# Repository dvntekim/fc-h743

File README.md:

# fc-h743 — STM32H743 flight controller for a GPS-denied learned-control quadrotor

> **DRAFT UNTIL INDEPENDENT REVIEW.** Not yet reviewed by a second engineer and not ordered.
> Work through [REVIEW.md](REVIEW.md) before anyone pays for boards.

· [Changelog](CHANGELOG.md) · [Build log](docs/BUILD_LOG.md) · [Design review](docs/design_review.md) · [Contributing](CONTRIBUTING.md)

**View it in the browser (no install):**
- Whole project (board + all 7 schematic sheets): <https://kicanvas.org/?github=https://github.com/dvntekim/fc-h743/tree/main/kicad>
- PCB only: <https://kicanvas.org/?github=https://github.com/dvntekim/fc-h743/blob/main/kicad/fc.kicad_pcb>
- PDF schematic: [docs/schematic.pdf](docs/schematic.pdf)

| Top | Bottom |
|---|---|
|  |  |

## What it is

A 50 × 50 mm, 6-layer flight controller (30.5 mm M3 mount) that runs PX4 on an STM32H743VIT6.
It is adapted from the Pixhawk FMUv6C reference design (same MCU family, LQFP-100, same PX4 pin
roles where possible) and built for indoor, GPS-denied flight with a learned (RAPTOR-style)
controller, so the electrical effort goes into clean sensing, timing and telemetry:

| Area | What is on the board | Why |
|---|---|---|
| Primary IMU | TDK ICM-45686 on SPI1, **clocked by a 32 kHz reference from TIM2_CH3 (PB10)** | Locks the IMU's ODR to the MCU clock: no sample-rate drift between IMU and controller. PX4 `icm45686 -C 32000` |
| Second IMU | Bosch BMI088 on its own bus (SPI2) | Vibration-robust accel; independent bus so one faulty sensor cannot stall the other |
| IMU thermal control | 4 × 120 Ω heater ring around both IMUs, AO3400A on PB9 | Holds the IMUs at 45 °C so bias does not drift with ambient (PX4 `HEATER1_TEMP`) |
| Barometer | Bosch BMP581 on I2C4 (0x47) | Lowest-noise MEMS baro in the class |
| CAN | 2 × TI TCAN1462V, CAN FD with signal improvement (8 Mbit/s) | DroneCAN/Cyphal sensors (flow, range) at FD rates |
| Motor outputs | 4 × bidirectional DShot on TIM1 + ESC serial telemetry (UART8) | RPM feedback for motor-aware learned control |
| Camera trigger | M7/M8 on TIM5 (capture/trigger) | Hardware timestamps for visual odometry |
| Power | TPS54360B 5.09 V buck (60 V in, switch node as a 26 mm² pour, boot loop 2.3 mm), ideal-diode OR with USB (2 × LM66100), TLV62569 3V3, LP5907 sensor LDO, 2 × TPS2553 current-limited switches | Sensor rail can be power-cycled from firmware (PB2) to recover a hung sensor |
| Storage / USB | microSD on SDMMC2 (4-bit), USB-C (FS) | Logs and parameters; PX4 console |

## What is real and what is simulated

Nothing on this page has been built. The board has passed every check that can run without
hardware: rule checks, a JLCPCB manufacturing check, field-solver, voltage-drop and thermal
models, a power-stage simulation, and PX4 booting on a simulated STM32H743 with this board's pin
map. Each model states its limits in its own file. The first built board must confirm the
numbers, starting with the bench plan in [REVIEW.md](REVIEW.md).

Rev B is in progress: [docs/revB_thermal.md](docs/revB_thermal.md) sets an IMU temperature
requirement from the datasheets and shows the IMUs must move off the MCU onto an isolated island
to meet it. The analysis is done; the layout is not.

## Verification status

| Check | Tool | Result |
|---|---|---|
| Electrical rules | KiCad 9 ERC | **0 errors, 0 warnings** |
| Design rules | KiCad 9 DRC (JLCPCB 6-layer limits, `kicad/fc.kicad_dru`) | **0 errors, 0 unconnected** (61 silkscreen-cosmetic warnings) |
| Schematic ↔ PCB parity | KiCad 9 DRC `--schematic-parity` | 0 issues |
| Vendor guides | every IC against its datasheet / layout guide | [docs/design_review.md](docs/design_review.md): 4 fixes made, 4 items open |
| Pin map | `scripts/pinmap_check.py` against ST's pin data (KiCad STM32H743VITx symbol) | **PASS**, 74 pins — [docs/pinmap.md](docs/pinmap.md) |
| BOM availability | JLCPCB parts API | 69/69 parts in stock on 2026-11-06 — [docs/bom_check.md](docs/bom_check.md) |
| 5 V buck loop | ngspice averaged current-mode model | crossover 19–35 kHz, phase margin ≥ 66.6°, gain margin ≥ 13.1 dB over 27 corners; load step 4.78–5.39 V — [docs/power_sim.md](docs/power_sim.md) |
| Impedance and crosstalk | atlc 2D field solver + scan of the routed board | USB 84.7 Ω diff; worst crosstalk 1.1 % — `sim/si` |
| DC voltage drop | resistive-mesh solver on the routed copper | VBAT ≤ 56 mV at 3 A, +3V3 ≤ 46 mV; +5V to the 5 V switches 235 mV at their limits (open) — `sim/pi` |
| Thermal | board conduction/convection model | 37–86 °C board; IMU heater cannot regulate (open) — `sim/thermal` |
| Firmware on the netlist | PX4 board port + Simantic STM32H743 simulator, scenario generated from the netlist | **PASS**: ICM-45686 on SPI1, BMI088 on SPI2, BMP581 on I2C4 @0x47, CAN1 RX, SD logger, NSH — [docs/verification.md](docs/verification.md) |
| Firmware build | PX4 at c0d2c54, GCC 13.2, Linux CI + macOS | builds, flash 91 % |
| Manufacturability | JLCDFM (JLCPCB online DFM) | 1 real finding fixed (vias near mounting holes), other flags within JLC's limits — [docs/design_review.md](docs/design_review.md); PCBWay pending |
| Independent review | second engineer | **not done** |

## Board

- **Stackup:** JLCPCB JLC06161H-3313D, 1.6 mm, ENIG (layer thicknesses checked against jlcpcb.com/impedance).
  F.Cu signal · In1 GND · In2 signal · In3 signal · In4 GND · B.Cu signal.
  Every signal layer sits 0.18–0.25 mm from its own GND plane; In2/In3 face each other across
  0.545 mm. Written into the board file (`Board Setup → Physical Stackup`).
- **USB D+/D−:** 0.25 mm / 0.15 mm gap on F.Cu over In1 ≈ 90 Ω differential (IPC-2141 estimate;
  confirm with JLCPCB's impedance calculator). USB FS is forgiving at this length.
- **Net classes:** HighCurrent (VBAT, switch node) 0.8 mm · Power 0.4 mm · Supply (3V3, VDDA) 0.3 mm ·
  signals 0.127 mm / 0.1 mm clearance · vias 0.45/0.2 mm, plus 20 at 0.35/0.15 mm of which 17 are via-in-pad
  (order with epoxy-filled, capped vias — JLC includes this on 6-layer boards; confirm on the quote).
- **Parts on both sides.** IMUs sit on the bottom inside the MCU's pin ring so their SPI runs are a few mm.
  Expected PX4 rotation `-R 6` (yaw 270°) — verify on the bench (REVIEW.md).

## Deviations from the spec doc (on purpose)

| Spec | Built | Reason |
|---|---|---|
| ≤ 38 × 38 mm | 50 × 50 mm | Courtyards alone filled 94 % of 38 × 38 with the frontier feature set (2 CAN FD, heater, two IMU buses, ideal-diode power path) |
| 4-layer | 6-layer | Two inner routing layers each next to a solid GND plane; needed to route LQFP-100 + both IMU buses at 50 × 50 |
| Top-side parts only | Both sides | IMUs under the MCU (short SPI, centroid placement); costs standard (not economic) assembly at JLCPCB |
| JLC04161H-3313 | JLC06161H-3313D | Follows from 6 layers |

## Repository

```
kicad/      KiCad 9 project (schematic, PCB, project library, DRC rules)
fab/        Gerber + drill zip, JLCPCB BOM and CPL, STEP
docs/       schematic PDF, renders, pin map, critical nets, power sim, design review, verification log,
            build log, BOM check, reports/
firmware/   PX4 board port: boards/dvntekim/fch743
sim/        simantic/ (PX4 boot scenario from the netlist), buck/ (ngspice), si/ (atlc field solver,
            crosstalk scan), pi/ (IR drop), thermal/ (board temperature)
scripts/    everything above is generated from these (design.py is the single source of truth)
.kibot/     KiBot config used by CI for the fab package, iBOM, PDF and STEP
.github/    CI workflow, issue and pull-request templates
REVIEW.md   checklist for the independent reviewer and for bring-up
CHANGELOG.md, CONTRIBUTING.md
```

How it was made: `scripts/design.py` (parts, nets, pin map) → `gen_lib.py` → `gen_sch.py` (schematic, ERC) →
`gen_pcb.py` (placement) → `prep_route.py` → Freerouting 1.9 → `import_ses.py`, then finishing passes
(`fix_route.py` local router, `stitch.py`/`island_fix.py` GND stitching, `rework_power.py`, `sw_zone.py`,
`vin_zone.py`) → `drc.sh` → `export.sh`. The schematic regenerates from `design.py`; after the hand-finishing,
**`kicad/fc.kicad_pcb` is the source of truth for the layout** (re-running `gen_pcb.py` starts a new layout).

## Licence

Copyright (c) 2026 Daniel Kim (dvntekim).

| What | Licence | File |
|---|---|---|
| Hardware: `kicad/`, `fab/`, design docs in `docs/` | CERN-OHL-P-2.0 | [LICENSE](LICENSE) |
| Firmware: `firmware/` (PX4 board port) | BSD-3-Clause, same as PX4 | [firmware/LICENSE](firmware/LICENSE) |
| Scripts, simulations, CI: `scripts/`, `sim/`, `.github/`, `.kibot/` | MIT | [LICENSE-MIT](LICENSE-MIT) |

Source location (CERN-OHL-P-2.0 section 3): https://github.com/dvntekim/fc-h743

The board, its design history and the files in this repository may be used to train models,
under the terms above.

## Ordering

Do not order until REVIEW.md is signed off and CI is green on the commit being ordered. Then upload `fab/fc-h743-gerbers.zip` to JLCPCB
(6 layers, 1.6 mm, JLC06161H-3313D, ENIG), add assembly with `fab/bom_jlc.csv` and `fab/cpl_jlc.csv`,
and check every rotation in the placement preview.

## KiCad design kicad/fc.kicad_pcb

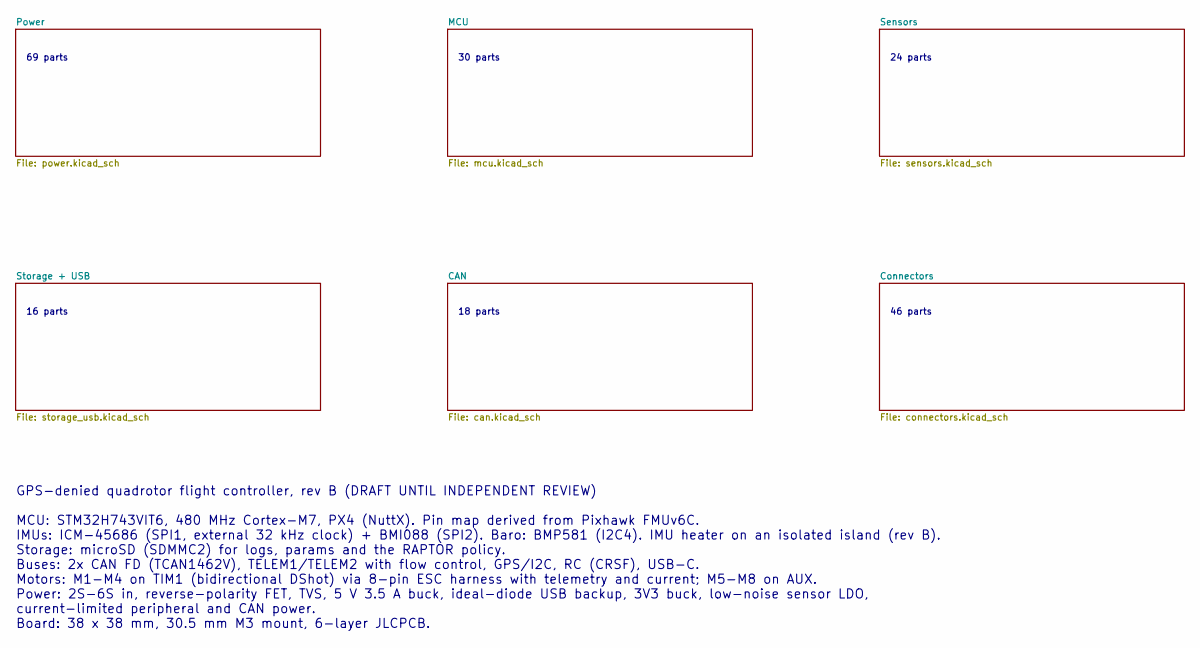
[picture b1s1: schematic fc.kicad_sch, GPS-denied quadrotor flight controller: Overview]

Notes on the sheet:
69 parts
30 parts
24 parts
16 parts
18 parts
46 parts
GPS-denied quadrotor flight controller, rev B (DRAFT UNTIL INDEPENDENT REVIEW) MCU: STM32H743VIT6, 480 MHz Cortex-M7, PX4 (NuttX). Pin map derived from Pixhawk FMUv6C. IMUs: ICM-45686 (SPI1, external 32 kHz clock) + BMI088 (SPI2). Baro: BMP581 (I2C4). IMU heater on an isolated island (rev B). Stora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

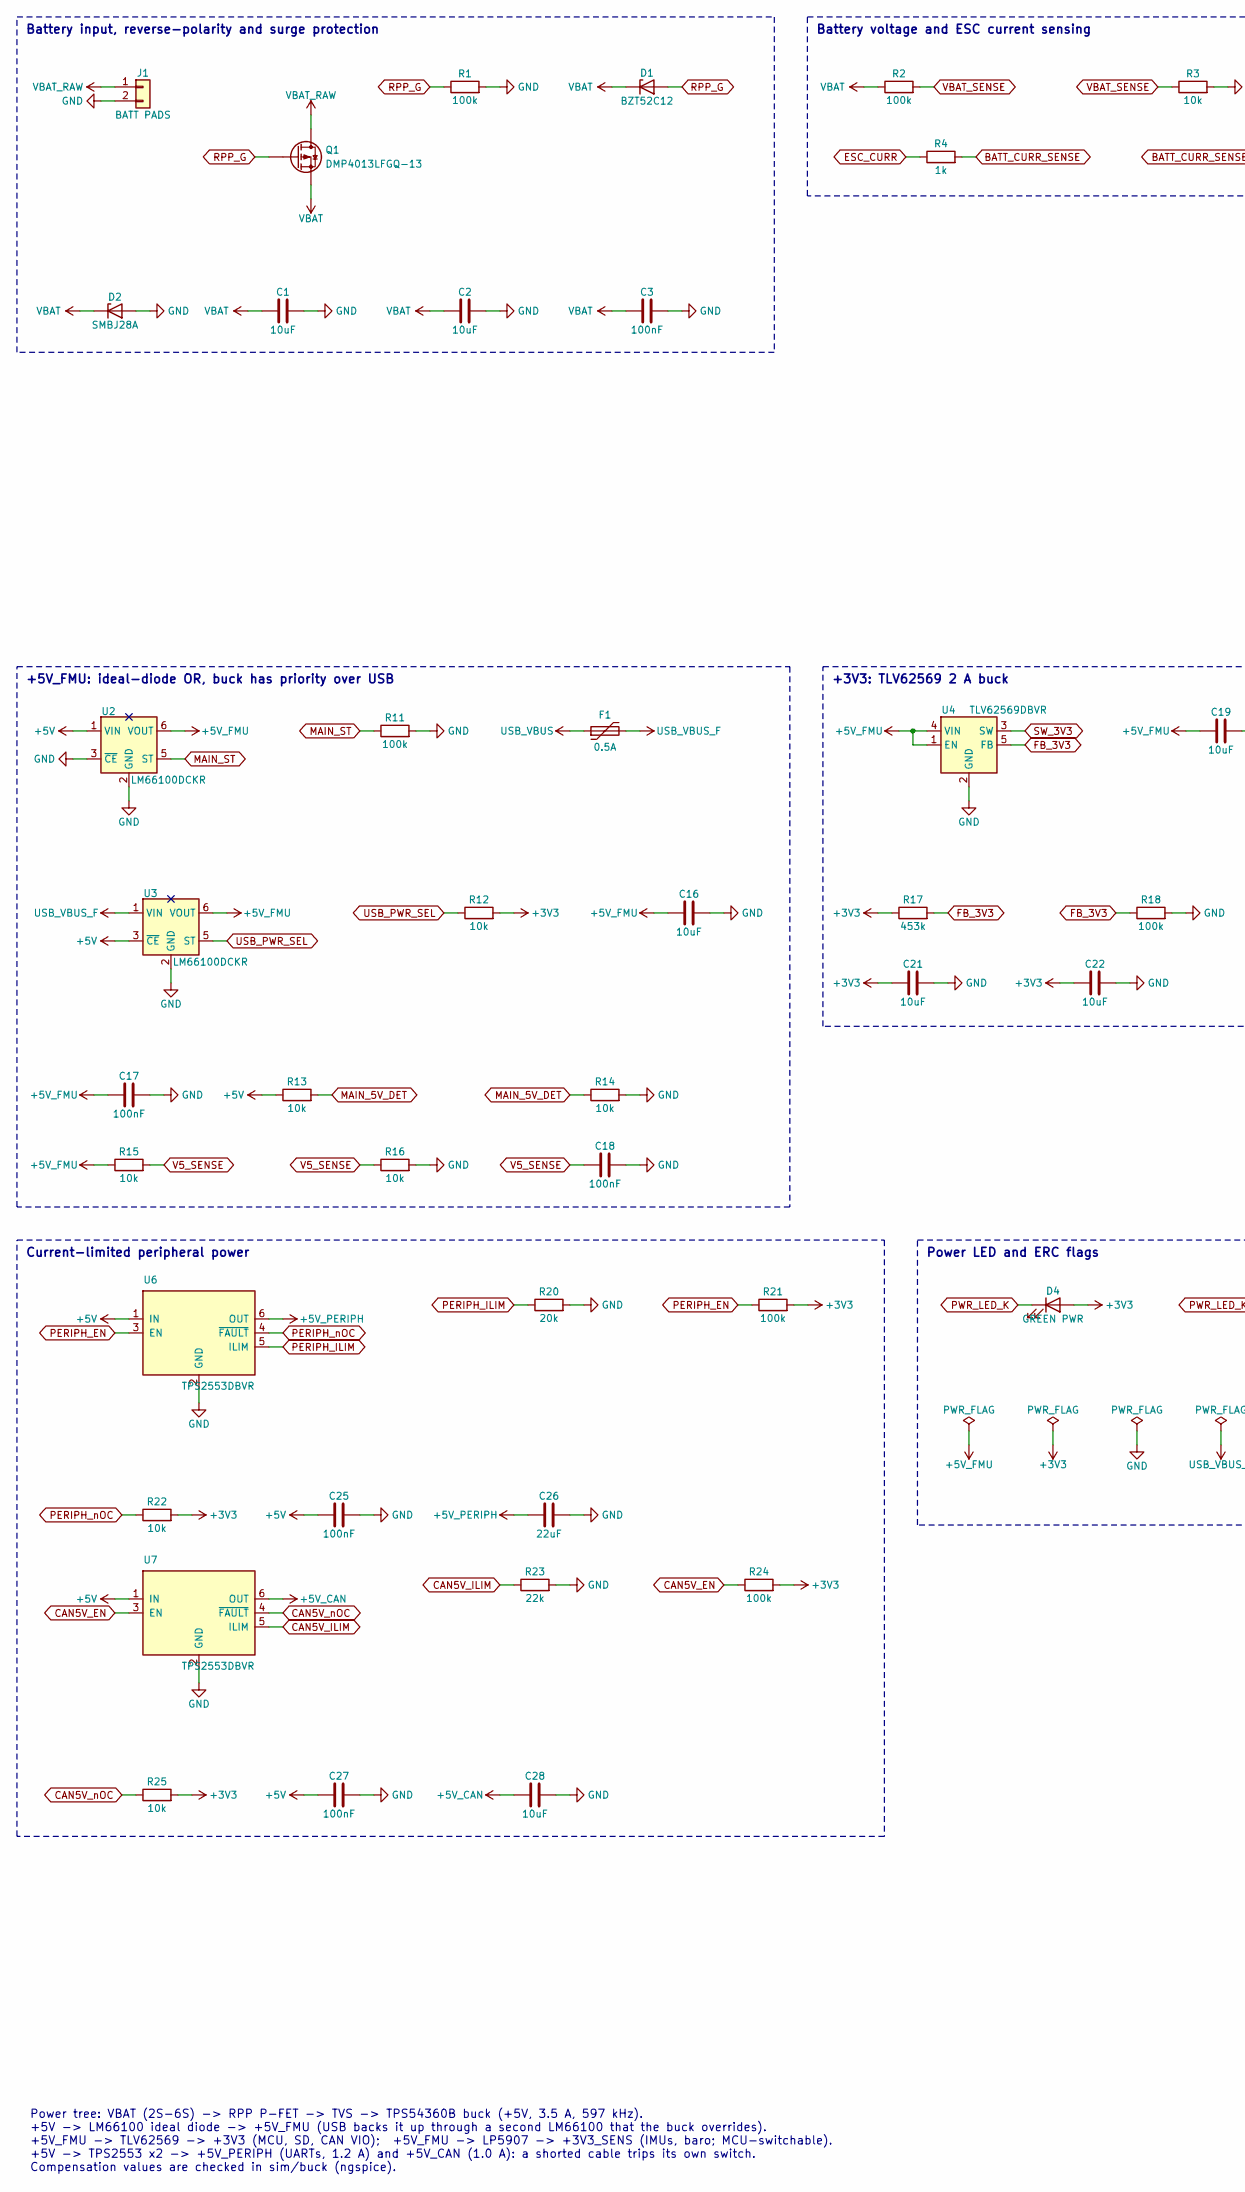
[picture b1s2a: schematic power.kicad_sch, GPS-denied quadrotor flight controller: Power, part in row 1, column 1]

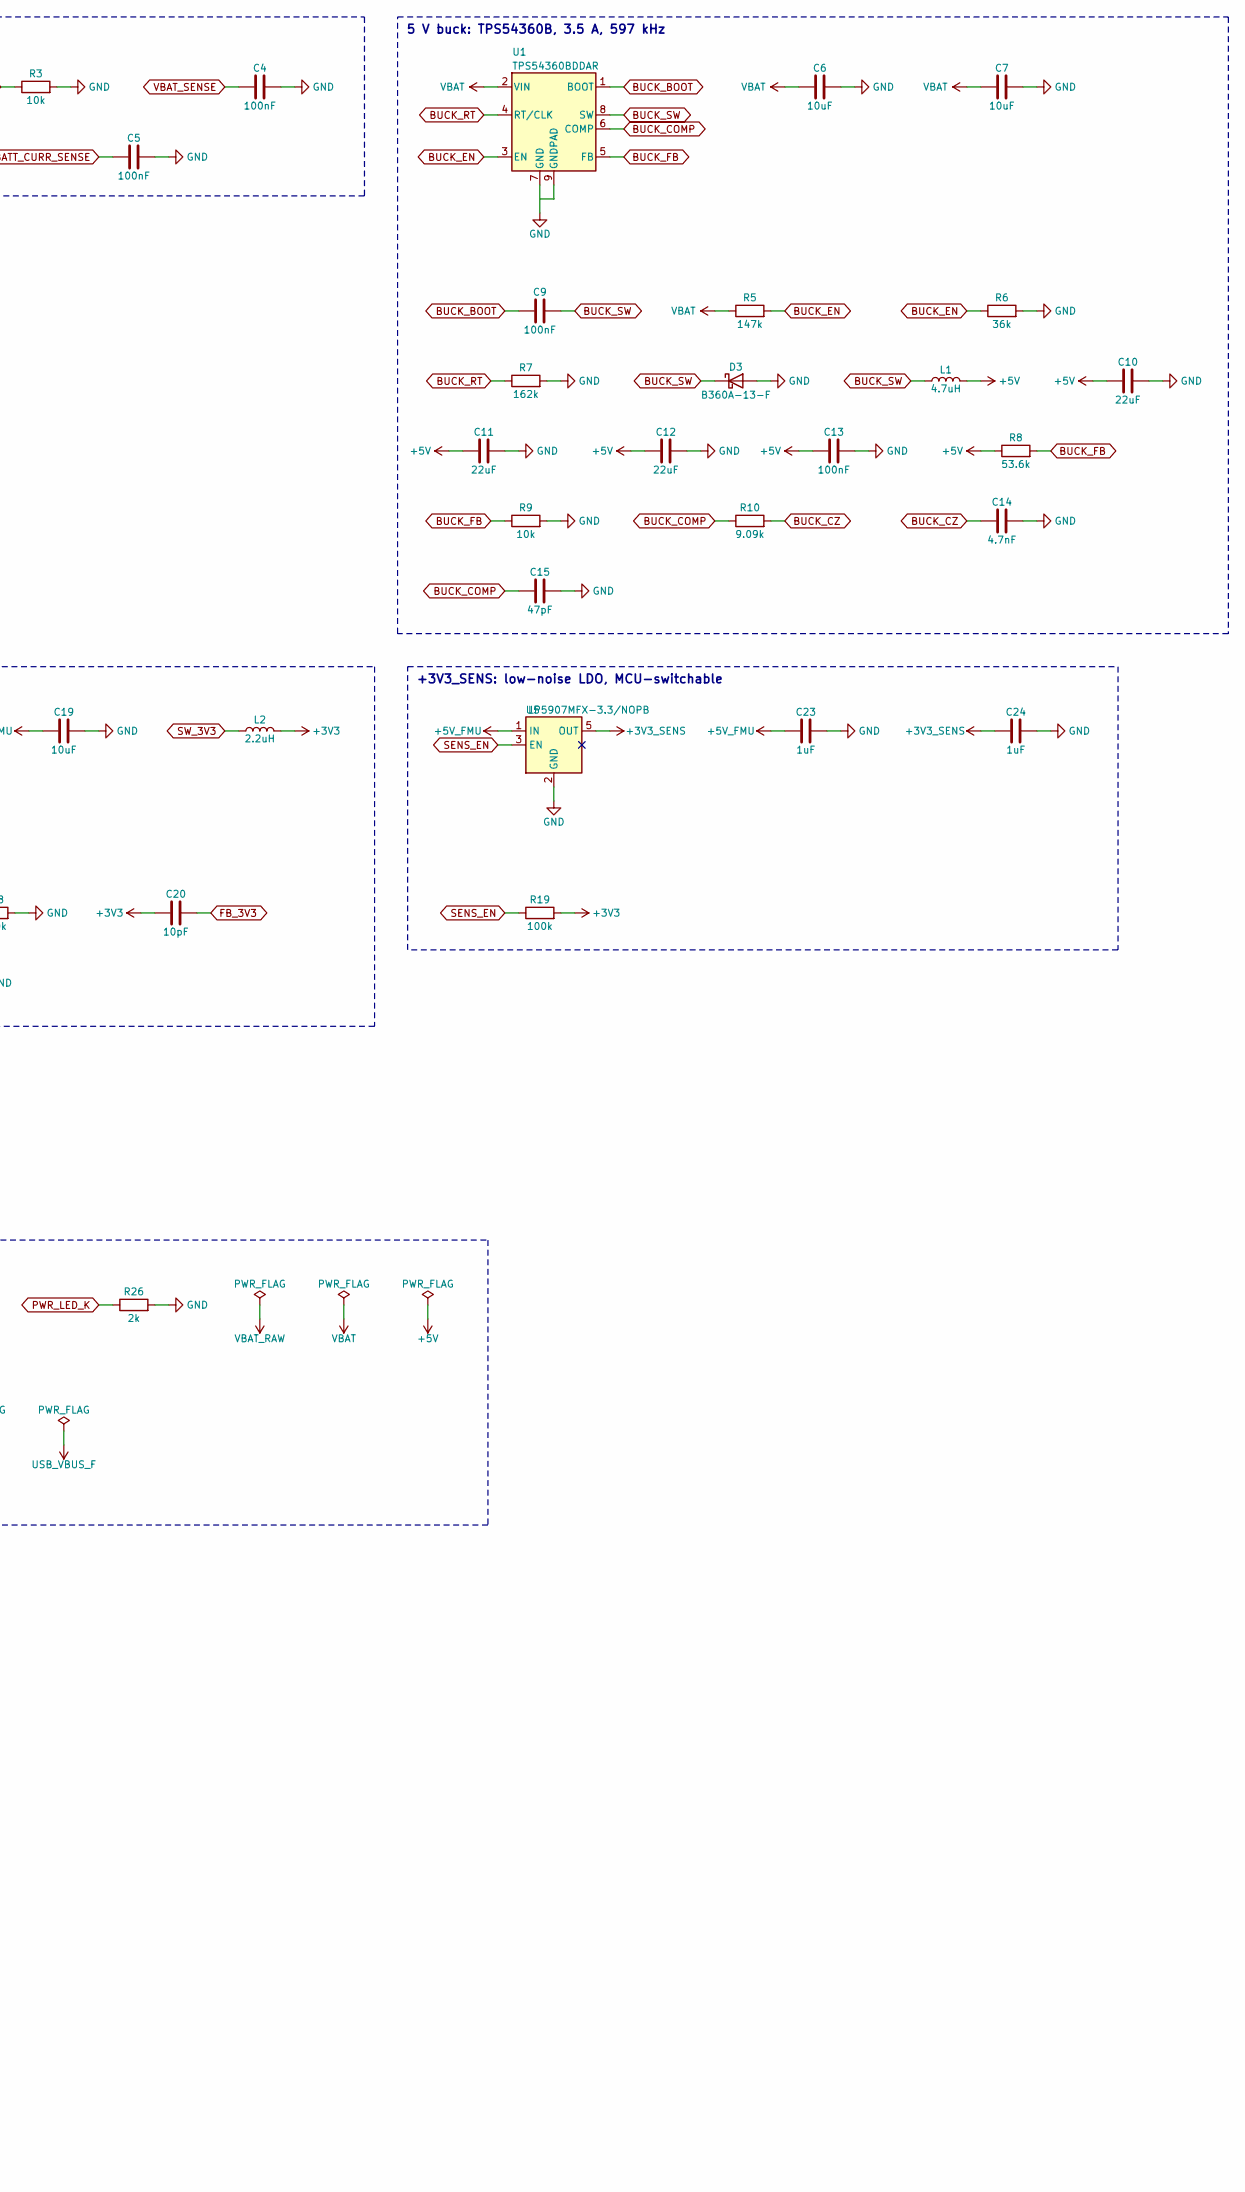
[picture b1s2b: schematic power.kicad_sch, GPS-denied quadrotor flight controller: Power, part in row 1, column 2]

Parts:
C1, C2, C6, C7: 10uF; C_0805_2012Metric; Rating 50V X5R; LCSC C440198
C3: 100nF; C_0603_1608Metric; Rating 50V X7R; LCSC C14663
C4, C5, C9, C13, C17, C18, C25, C27: 100nF; C_0402_1005Metric; Rating 16V X7R; LCSC C1525
C10, C11, C12, C26: 22uF; C_0805_2012Metric; Rating 25V X5R; LCSC C45783
C14: 4.7nF; C_0402_1005Metric; Rating 50V X7R; LCSC C1538
C15: 47pF; C_0402_1005Metric; Rating 50V C0G; LCSC C1567
C16, C19, C21, C22, C28: 10uF; C_0603_1608Metric; Rating 10V X5R; LCSC C19702
C20: 10pF; C_0402_1005Metric; Rating 50V C0G; LCSC C32949
C23, C24: 1uF; C_0402_1005Metric; Rating 25V X5R; LCSC C52923
D1: BZT52C12; D_SOD-123; LCSC C43491
D2: SMBJ28A; D_SMB; LCSC C113997
D3: B360A-13-F; D_SMA; LCSC C94193
D4: GREEN PWR; LED_0603_1608Metric; LCSC C2986059
F1: 0.5A; Fuse_1206_3216Metric; LCSC C69688
J1: BATT PADS; PowerPads_2x_3x5mm
L1: 4.7uH; L_Changjiang_FXL0530; LCSC C177246
L2: 2.2uH; L_1008_2520Metric; LCSC C98350
Q1: DMP4013LFGQ-13; Diodes_PowerDI3333-8; LCSC C7264680
R1, R2, R11, R18, R19, R21, R24: 100k; R_0402_1005Metric; LCSC C25741
R3, R9, R12, R13, R14, R15, R16, R22, R25: 10k; R_0402_1005Metric; LCSC C25744
R4: 1k; R_0402_1005Metric; LCSC C11702
R5: 147k; R_0402_1005Metric; LCSC C64171
R6: 36k; R_0402_1005Metric; LCSC C43676
R7: 162k; R_0402_1005Metric; LCSC C54068
R8: 53.6k; R_0402_1005Metric; LCSC C53398
R10: 9.09k; R_0402_1005Metric; LCSC C11549
R17: 453k; R_0402_1005Metric; LCSC C27009
R20: 20k; R_0402_1005Metric; LCSC C25765
R23: 22k; R_0402_1005Metric; LCSC C25768
R26: 2k; R_0402_1005Metric; LCSC C4109
U1: TPS54360BDDAR; TI_SO-PowerPAD-8_ThermalVias; LCSC C524806
U2, U3: LM66100DCKR; SOT-363_SC-70-6; LCSC C2869734
U4: TLV62569DBVR; SOT-23-5; LCSC C141836
U5: LP5907MFX-3.3/NOPB; SOT-23-5; LCSC C80670
U6, U7: TPS2553DBVR; SOT-23-6; LCSC C55266

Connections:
+3V3: C20.1, C21.1, C22.1, D4.2 (A), L2.2, R12.2, R17.1, R19.2, R21.2, R22.2, R24.2, R25.2; also elsewhere on the board
+3V3_SENS: C24.1, U5.5 (OUT); also elsewhere on the board
+5V: C10.1, C11.1, C12.1, C13.1, C25.1, C27.1, L1.2, R8.1, R13.1, U2.1 (VIN), U3.3 (~CE), U6.1 (IN), U7.1 (IN); also elsewhere on the board
+5V_CAN: C28.1, U7.6 (OUT); also elsewhere on the board
+5V_FMU: C16.1, C17.1, C19.1, C23.1, R15.1, U2.6 (VOUT), U3.6 (VOUT), U4.1 (EN), U4.4 (VIN), U5.1 (IN); also elsewhere on the board
+5V_PERIPH: C26.1, U6.6 (OUT); also elsewhere on the board
BATT_CURR_SENSE: C5.1, R4.2; also elsewhere on the board
BUCK_BOOT: C9.1, U1.1 (BOOT)
BUCK_COMP: C15.1, R10.1, U1.6 (COMP)
BUCK_CZ: C14.1, R10.2
BUCK_EN: R5.2, R6.1, U1.3 (EN)
BUCK_FB: R8.2, R9.1, U1.5 (FB)
BUCK_RT: R7.1, U1.4 (RT/CLK)
BUCK_SW: C9.2, D3.1 (K), L1.1, U1.8 (SW)
CAN5V_EN: R24.1, U7.3 (EN); also elsewhere on the board
CAN5V_ILIM: R23.1, U7.5 (ILIM)
CAN5V_nOC: R25.1, U7.4 (~FAULT); also elsewhere on the board
ESC_CURR: R4.1; also elsewhere on the board
FB_3V3: C20.2, R17.2, R18.1, U4.5 (FB)
GND: C1.2, C2.2, C3.2, C4.2, C5.2, C6.2, C7.2, C10.2, C11.2, C12.2, C13.2, C14.2, C15.2, C16.2, C17.2, C18.2, C19.2, C21.2, C22.2, C23.2, C24.2, C25.2, C26.2, C27.2, C28.2, D2.2 (A), D3.2 (A), J1.2, R1.2, R3.2, R6.2, R7.2, R9.2, R11.2, R14.2, R16.2, R18.2, R20.2, R23.2, R26.2, U1.7 (GND), U1.9 (GNDPAD), U2.2 (GND), U2.3 (~CE), U3.2 (GND), U4.2 (GND), U5.2 (GND), U6.2 (GND), U7.2 (GND); also elsewhere on the board
MAIN_5V_DET: R13.2, R14.1; also elsewhere on the board
MAIN_ST: R11.1, U2.5 (ST)
PERIPH_EN: R21.1, U6.3 (EN); also elsewhere on the board
PERIPH_ILIM: R20.1, U6.5 (ILIM)
PERIPH_nOC: R22.1, U6.4 (~FAULT); also elsewhere on the board
PWR_LED_K: D4.1 (K), R26.1
RPP_G: D1.2 (A), Q1.4 (G), R1.1
SENS_EN: R19.1, U5.3 (EN); also elsewhere on the board
SW_3V3: L2.1, U4.3 (SW)
USB_PWR_SEL: R12.1, U3.5 (ST); also elsewhere on the board
USB_VBUS: F1.1; also elsewhere on the board
USB_VBUS_F: F1.2, U3.1 (VIN)
V5_SENSE: C18.1, R15.2, R16.1; also elsewhere on the board
VBAT: C1.1, C2.1, C3.1, C6.1, C7.1, D1.1 (K), D2.1 (K), Q1.1 (S), Q1.2 (S), Q1.3 (S), R2.1, R5.1, U1.2 (VIN); also elsewhere on the board
VBAT_RAW: J1.1, Q1.5 (D); also elsewhere on the board
VBAT_SENSE: C4.1, R2.2, R3.1; also elsewhere on the board

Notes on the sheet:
Battery input, reverse-polarity and surge protection
Battery voltage and ESC current sensing
5 V buck: TPS54360B, 3.5 A, 597 kHz
+5V_FMU: ideal-diode OR, buck has priority over USB
+3V3: TLV62569 2 A buck
+3V3_SENS: low-noise LDO, MCU-switchable
Current-limited peripheral power
Power LED and ERC flags
Power tree: VBAT (2S-6S) -> RPP P-FET -> TVS -> TPS54360B buck (+5V, 3.5 A, 597 kHz). +5V -> LM66100 ideal diode -> +5V_FMU (USB backs it up through a second LM66100 that the buck overrides). +5V_FMU -> TLV62569 -> +3V3 (MCU, SD, CAN VIO); +5V_FMU -> LP5907 -> +3V3_SENS (IMUs, baro; MCU-switchable)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

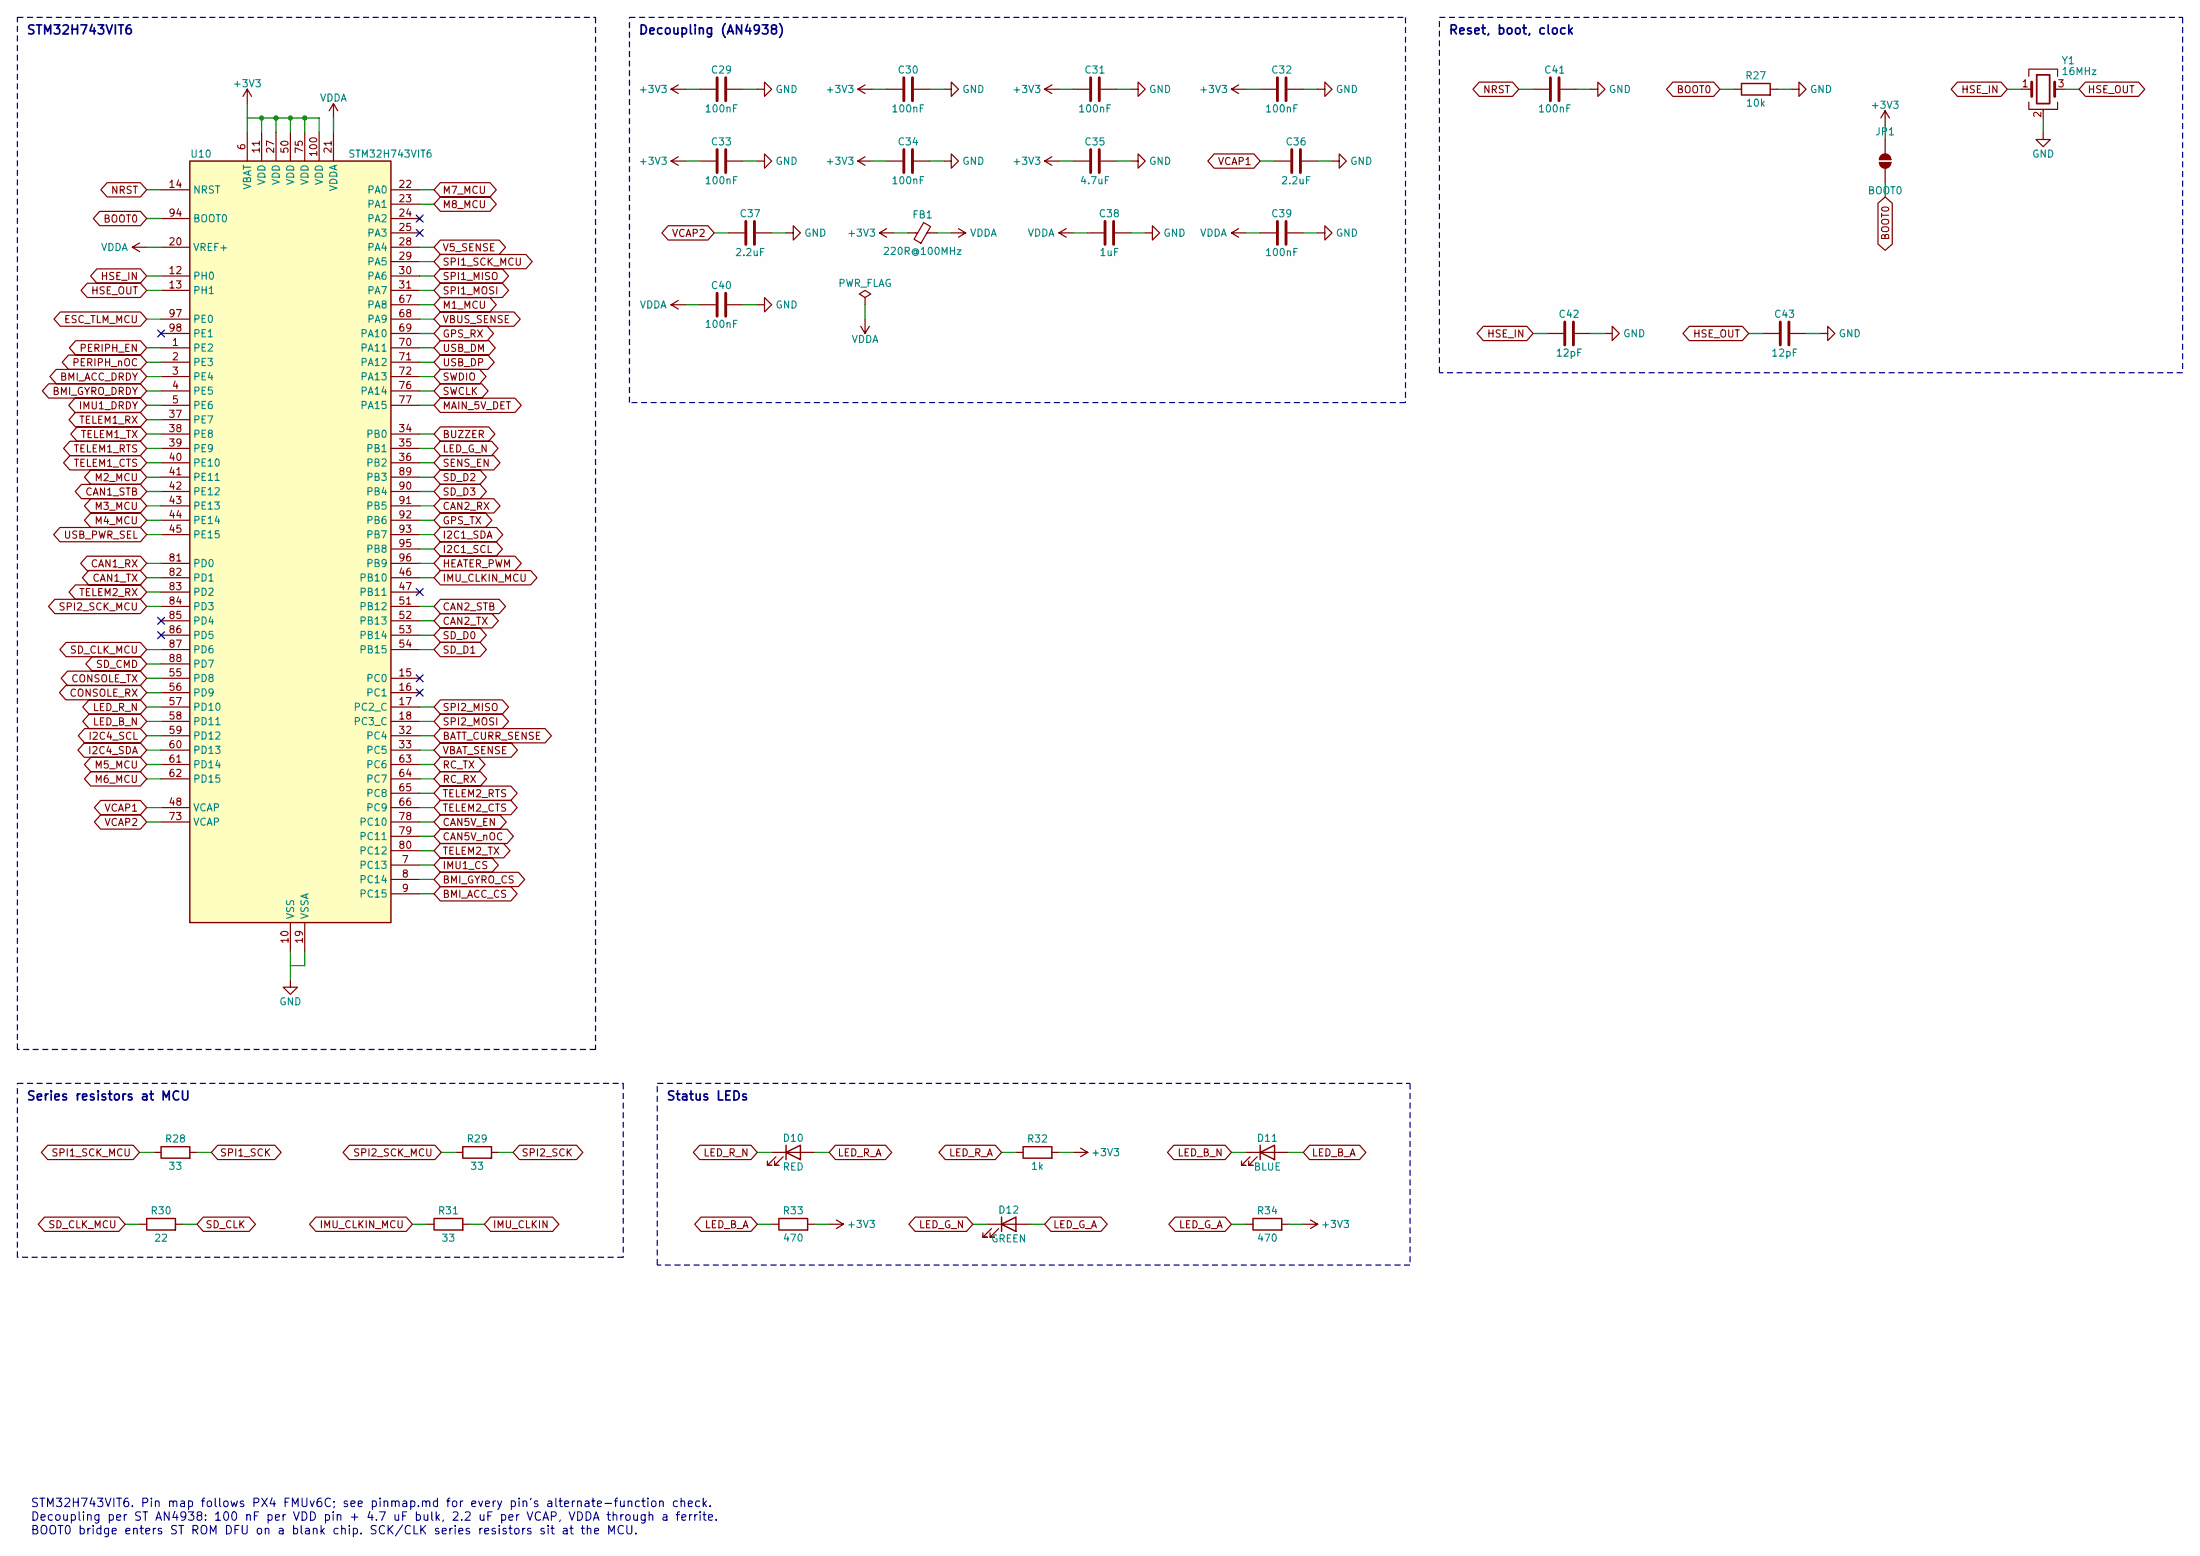
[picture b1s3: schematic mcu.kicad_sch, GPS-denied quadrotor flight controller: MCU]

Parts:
C29, C30, C31, C32, C33, C34, C39, C40, C41: 100nF; C_0402_1005Metric; Rating 16V X7R; LCSC C1525
C35: 4.7uF; C_0603_1608Metric; Rating 25V X5R; LCSC C19666
C36, C37: 2.2uF; C_0402_1005Metric; Rating 10V X5R; LCSC C12530
C38: 1uF; C_0402_1005Metric; Rating 25V X5R; LCSC C52923
C42, C43: 12pF; C_0402_1005Metric; Rating 50V C0G; LCSC C1547
D10: RED; LED_0603_1608Metric; LCSC C2286
D11: BLUE; LED_0603_1608Metric; LCSC C965807
D12: GREEN; LED_0603_1608Metric; LCSC C2986059
FB1: 220R@100MHz; L_0402_1005Metric; LCSC C76885
JP1: BOOT0; SolderJumper-2_P1.3mm_Open_RoundedPad1.0x1.5mm
R27: 10k; R_0402_1005Metric; LCSC C25744
R28, R29, R31: 33; R_0402_1005Metric; LCSC C25105
R30: 22; R_0402_1005Metric; LCSC C25092
R32: 1k; R_0402_1005Metric; LCSC C11702
R33, R34: 470; R_0402_1005Metric; LCSC C25117
U10: STM32H743VIT6; LQFP-100_14x14mm_P0.5mm; LCSC C114409
Y1: 16MHz; Crystal_SMD_3225-4Pin_3.2x2.5mm; LCSC C13738

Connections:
+3V3: C29.1, C30.1, C31.1, C32.1, C33.1, C34.1, C35.1, FB1.1, JP1.2 (B), R32.2, R33.2, R34.2, U10.6 (VBAT), U10.11 (VDD), U10.27 (VDD), U10.50 (VDD), U10.75 (VDD), U10.100 (VDD); also elsewhere on the board
BATT_CURR_SENSE: U10.32 (PC4); also elsewhere on the board
BMI_ACC_CS: U10.9 (PC15); also elsewhere on the board
BMI_ACC_DRDY: U10.3 (PE4); also elsewhere on the board
BMI_GYRO_CS: U10.8 (PC14); also elsewhere on the board
BMI_GYRO_DRDY: U10.4 (PE5); also elsewhere on the board
BOOT0: JP1.1 (A), R27.1, U10.94 (BOOT0)
BUZZER: U10.34 (PB0); also elsewhere on the board
CAN1_RX: U10.81 (PD0); also elsewhere on the board
CAN1_STB: U10.42 (PE12); also elsewhere on the board
CAN1_TX: U10.82 (PD1); also elsewhere on the board
CAN2_RX: U10.91 (PB5); also elsewhere on the board
CAN2_STB: U10.51 (PB12); also elsewhere on the board
CAN2_TX: U10.52 (PB13); also elsewhere on the board
CAN5V_EN: U10.78 (PC10); also elsewhere on the board
CAN5V_nOC: U10.79 (PC11); also elsewhere on the board
CONSOLE_RX: U10.56 (PD9); also elsewhere on the board
CONSOLE_TX: U10.55 (PD8); also elsewhere on the board
ESC_TLM_MCU: U10.97 (PE0); also elsewhere on the board
GND: C29.2, C30.2, C31.2, C32.2, C33.2, C34.2, C35.2, C36.2, C37.2, C38.2, C39.2, C40.2, C41.2, C42.2, C43.2, R27.2, U10.10 (VSS), U10.19 (VSSA), U10.26 (VSS), U10.49 (VSS), U10.74 (VSS), U10.99 (VSS), Y1.2 (G), Y1.4 (G); also elsewhere on the board
GPS_RX: U10.69 (PA10); also elsewhere on the board
GPS_TX: U10.92 (PB6); also elsewhere on the board
HEATER_PWM: U10.96 (PB9); also elsewhere on the board
HSE_IN: C42.1, U10.12 (PH0), Y1.1
HSE_OUT: C43.1, U10.13 (PH1), Y1.3
I2C1_SCL: U10.95 (PB8); also elsewhere on the board
I2C1_SDA: U10.93 (PB7); also elsewhere on the board
I2C4_SCL: U10.59 (PD12); also elsewhere on the board
I2C4_SDA: U10.60 (PD13); also elsewhere on the board
IMU1_CS: U10.7 (PC13); also elsewhere on the board
IMU1_DRDY: U10.5 (PE6); also elsewhere on the board
IMU_CLKIN: R31.2; also elsewhere on the board
IMU_CLKIN_MCU: R31.1, U10.46 (PB10)
LED_B_A: D11.2 (A), R33.1
LED_B_N: D11.1 (K), U10.58 (PD11)
LED_G_A: D12.2 (A), R34.1
LED_G_N: D12.1 (K), U10.35 (PB1)
LED_R_A: D10.2 (A), R32.1
LED_R_N: D10.1 (K), U10.57 (PD10)
M1_MCU: U10.67 (PA8); also elsewhere on the board
M2_MCU: U10.41 (PE11); also elsewhere on the board
M3_MCU: U10.43 (PE13); also elsewhere on the board
M4_MCU: U10.44 (PE14); also elsewhere on the board
M5_MCU: U10.61 (PD14); also elsewhere on the board
M6_MCU: U10.62 (PD15); also elsewhere on the board
M7_MCU: U10.22 (PA0); also elsewhere on the board
M8_MCU: U10.23 (PA1); also elsewhere on the board
MAIN_5V_DET: U10.77 (PA15); also elsewhere on the board
NRST: C41.1, U10.14 (NRST); also elsewhere on the board
PERIPH_EN: U10.1 (PE2); also elsewhere on the board
PERIPH_nOC: U10.2 (PE3); also elsewhere on the board
RC_RX: U10.64 (PC7); also elsewhere on the board
RC_TX: U10.63 (PC6); also elsewhere on the board
SD_CLK: R30.2; also elsewhere on the board
SD_CLK_MCU: R30.1, U10.87 (PD6)
SD_CMD: U10.88 (PD7); also elsewhere on the board
SD_D0: U10.53 (PB14); also elsewhere on the board
SD_D1: U10.54 (PB15); also elsewhere on the board
SD_D2: U10.89 (PB3); also elsewhere on the board
SD_D3: U10.90 (PB4); also elsewhere on the board
SENS_EN: U10.36 (PB2); also elsewhere on the board
SPI1_MISO: U10.30 (PA6); also elsewhere on the board
SPI1_MOSI: U10.31 (PA7); also elsewhere on the board
SPI1_SCK: R28.2; also elsewhere on the board
SPI1_SCK_MCU: R28.1, U10.29 (PA5)
SPI2_MISO: U10.17 (PC2_C); also elsewhere on the board
SPI2_MOSI: U10.18 (PC3_C); also elsewhere on the board
SPI2_SCK: R29.2; also elsewhere on the board
SPI2_SCK_MCU: R29.1, U10.84 (PD3)
SWCLK: U10.76 (PA14); also elsewhere on the board
SWDIO: U10.72 (PA13); also elsewhere on the board
TELEM1_CTS: U10.40 (PE10); also elsewhere on the board
TELEM1_RTS: U10.39 (PE9); also elsewhere on the board
TELEM1_RX: U10.37 (PE7); also elsewhere on the board
TELEM1_TX: U10.38 (PE8); also elsewhere on the board
TELEM2_CTS: U10.66 (PC9); also elsewhere on the board
TELEM2_RTS: U10.65 (PC8); also elsewhere on the board
TELEM2_RX: U10.83 (PD2); also elsewhere on the board
TELEM2_TX: U10.80 (PC12); also elsewhere on the board
USB_DM: U10.70 (PA11); also elsewhere on the board
USB_DP: U10.71 (PA12); also elsewhere on the board
USB_PWR_SEL: U10.45 (PE15); also elsewhere on the board
V5_SENSE: U10.28 (PA4); also elsewhere on the board
VBAT_SENSE: U10.33 (PC5); also elsewhere on the board
VBUS_SENSE: U10.68 (PA9); also elsewhere on the board
VCAP1: C36.1, U10.48 (VCAP)
VCAP2: C37.1, U10.73 (VCAP)
VDDA: C38.1, C39.1, C40.1, FB1.2, U10.20 (VREF+), U10.21 (VDDA)

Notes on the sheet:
STM32H743VIT6
Decoupling (AN4938)
Reset, boot, clock
Series resistors at MCU
Status LEDs
STM32H743VIT6. Pin map follows PX4 FMUv6C; see pinmap.md for every pin's alternate-function check. Decoupling per ST AN4938: 100 nF per VDD pin + 4.7 uF bulk, 2.2 uF per VCAP, VDDA through a ferrite. BOOT0 bridge enters ST ROM DFU on a blank chip. SCK/CLK series resistors sit at the MCU.
